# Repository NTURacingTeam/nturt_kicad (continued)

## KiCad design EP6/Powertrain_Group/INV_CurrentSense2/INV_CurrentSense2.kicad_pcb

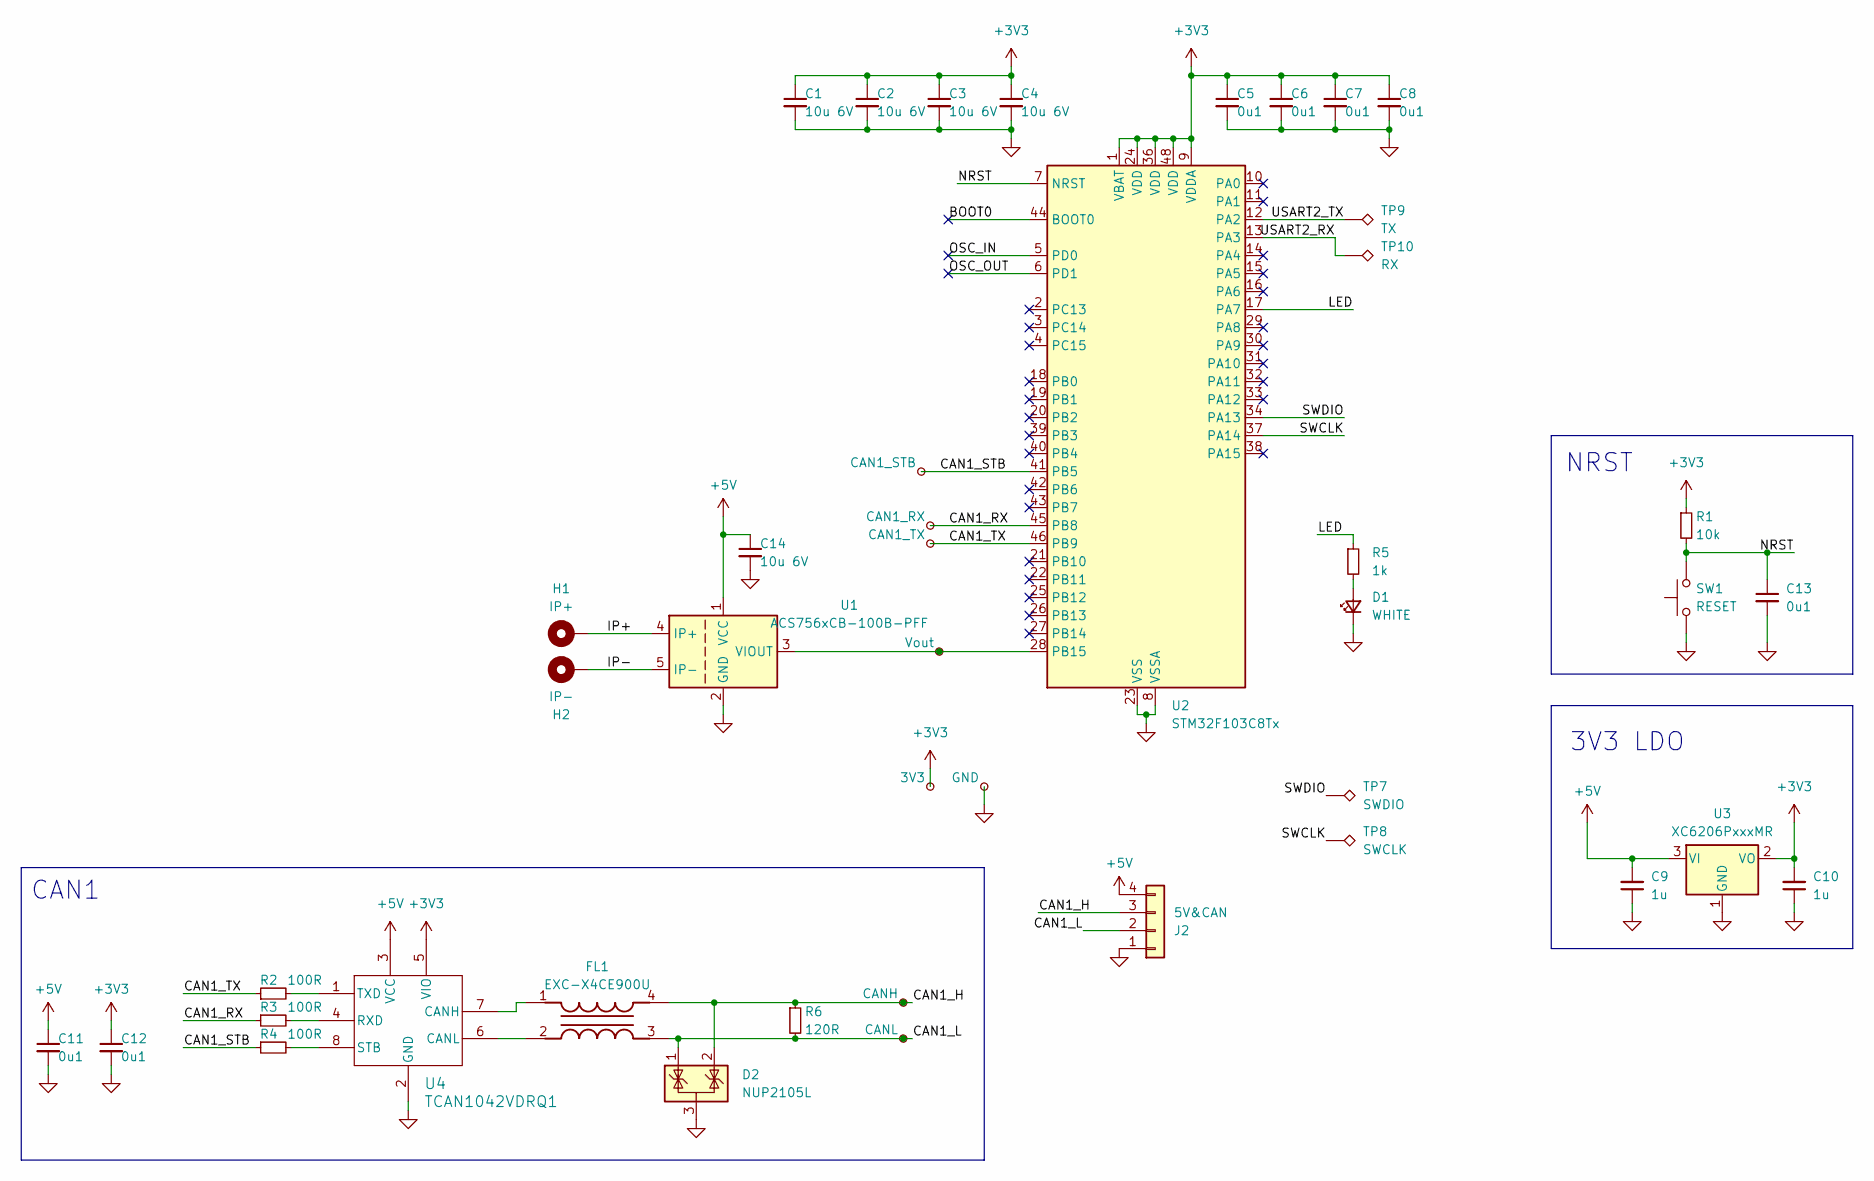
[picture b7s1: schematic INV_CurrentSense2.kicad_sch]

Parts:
C1, C2, C3, C4, C14: 10u 6V; C_0402_1005Metric
C5, C6, C7, C8, C11, C12, C13: 0u1; C_0402_1005Metric
C9, C10: 1u; C_0402_1005Metric
D1: WHITE; LED_0603_1608Metric
D2: NUP2105L; SOT-23
FL1: EXC-X4CE900U; EXCX4CE900U; Mouser Part Number 667-EXC-X4CE900U
H1: IP+; MountingHole_5.5mm_Pad_Via_15mm_square
H2: IP-; MountingHole_5.5mm_Pad_Via
J2: 5V&CAN; JST_XH_S4B-XH-A_1x04_P2.50mm_Horizontal
R1: 10k; R_0402_1005Metric
R2, R3, R4: 100R; R_0402_1005Metric
R5: 1k; R_0603_1608Metric
R6: 120R; R_0402_1005Metric
SW1: RESET; SW_Tactile_SPST_NO_Straight_CK_PTS636Sx25SMTRLFS
TP1: Vout; TestPoint_THTPad_D1.0mm_Drill0.5mm
TP2: CAN1_STB; TestPoint_THTPad_D1.0mm_Drill0.5mm
TP3: CANH; TestPoint_Pad_1.0x1.0mm
TP4: CANL; TestPoint_Pad_1.0x1.0mm
TP5: CAN1_RX; TestPoint_THTPad_D1.0mm_Drill0.5mm
TP6: CAN1_TX; TestPoint_THTPad_D1.0mm_Drill0.5mm
TP7: SWDIO; TestPoint_Pad_1.5x1.5mm
TP8: SWCLK; TestPoint_Pad_1.5x1.5mm
TP9: TX; TestPoint_Pad_1.0x1.0mm
TP10: RX; TestPoint_Pad_1.0x1.0mm
TP11: 3V3; TestPoint_THTPad_D1.0mm_Drill0.5mm
TP12: GND; TestPoint_THTPad_D1.0mm_Drill0.5mm
U1: ACS756xCB-100B-PFF; Allegro_CB_PFF
U2: STM32F103C8Tx; LQFP-48_7x7mm_P0.5mm
U3: XC6206PxxxMR; SOT-23-3
U4: TCAN1042VDRQ1; SOIC-8_3.9x4.9mm_P1.27mm

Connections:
+3V3: C1.1, C2.1, C3.1, C4.1, C5.1, C6.1, C7.1, C8.1, C10.2, C12.1, R1.1, TP11.1, U2.1 (VBAT), U2.9 (VDDA), U2.24 (VDD), U2.36 (VDD), U2.48 (VDD), U3.2 (VO), U4.5 (VIO)
+5V: C9.2, C11.1, C14.1, J2.4, U1.1 (VCC), U3.3 (VI), U4.3 (VCC)
/BOOT0: U2.44 (BOOT0)
/CAN1_H: D2.2 (K), FL1.4, J2.3, R6.1, TP3.1
/CAN1_L: D2.1 (K), FL1.3, J2.2, R6.2, TP4.1
/CAN1_RX: R3.1, TP5.1, U2.45 (PB8)
/CAN1_STB: R4.1, TP2.1, U2.41 (PB5)
/CAN1_TX: R2.1, TP6.1, U2.46 (PB9)
/IP+: H1.1, U1.4 (IP+)
/IP-: H2.1, U1.5 (IP-)
/LED: R5.1, U2.17 (PA7)
/NRST: C13.1, R1.2, SW1.2, U2.7 (NRST)
/OSC_IN: U2.5 (PD0)
/OSC_OUT: U2.6 (PD1)
/SWCLK: TP8.1, U2.37 (PA14)
/SWDIO: TP7.1, U2.34 (PA13)
/USART2_RX: TP10.1, U2.13 (PA3)
/USART2_TX: TP9.1, U2.12 (PA2)
GND: C1.2, C2.2, C3.2, C4.2, C5.2, C6.2, C7.2, C8.2, C9.1, C10.1, C11.2, C12.2, C13.2, C14.2, D1.1 (K), D2.3 (A), J2.1, SW1.1, TP12.1, U1.2 (GND), U2.8 (VSSA), U2.23 (VSS), U2.35 (VSS), U2.47 (VSS), U3.1 (GND), U4.2 (GND)
unnamed: D1.2 (A), R5.2
unnamed: TP1.1, U1.3 (VIOUT), U2.28 (PB15)
unnamed: FL1.1, U4.7 (CANH)
unnamed: FL1.2, U4.6 (CANL)
unnamed: R3.2, U4.4 (RXD)
unnamed: R4.2, U4.8 (STB)
unnamed: R2.2, U4.1 (TXD)

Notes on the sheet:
3V3 LDO
CAN1
NRST

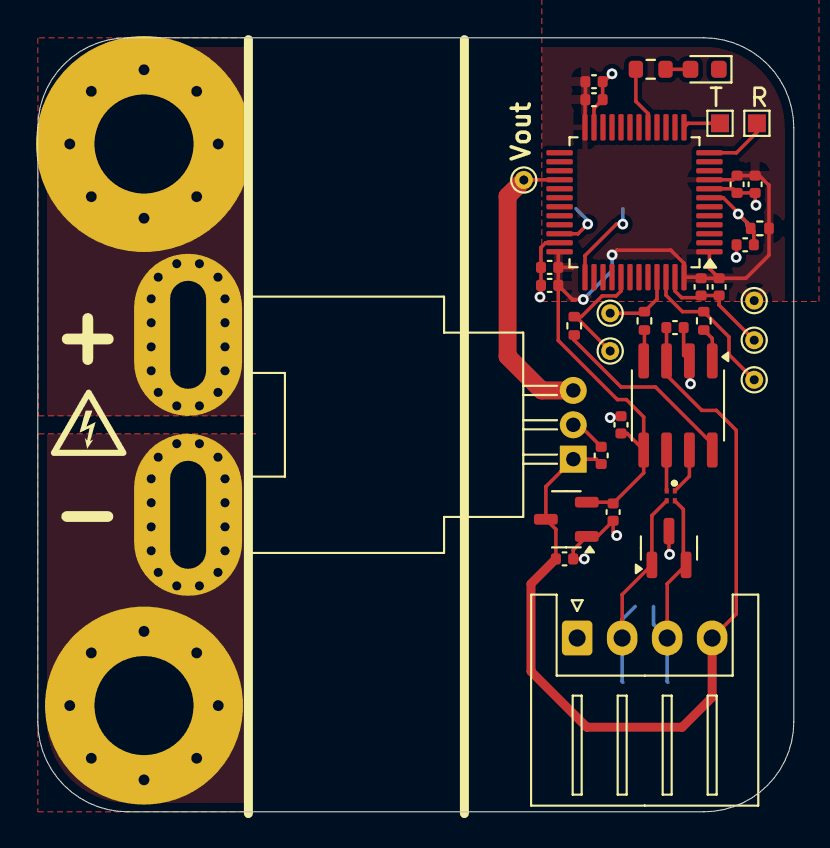
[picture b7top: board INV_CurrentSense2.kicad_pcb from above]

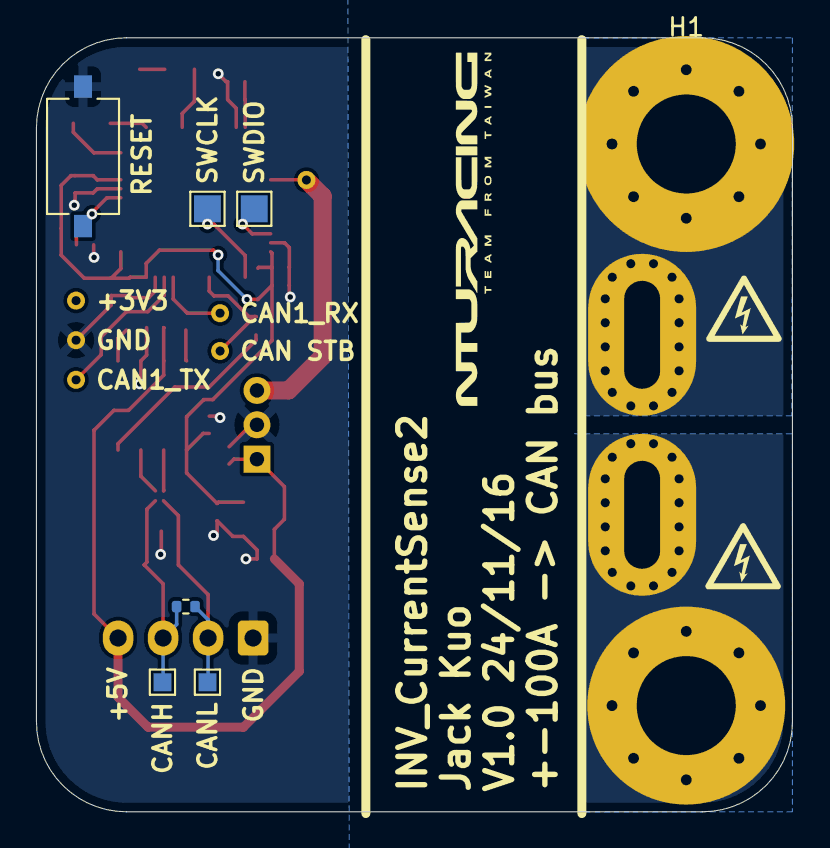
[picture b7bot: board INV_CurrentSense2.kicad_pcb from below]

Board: 2 copper layers, 42.0 x 43.0 mm, 43 parts (7 on the bottom side), 23 nets.

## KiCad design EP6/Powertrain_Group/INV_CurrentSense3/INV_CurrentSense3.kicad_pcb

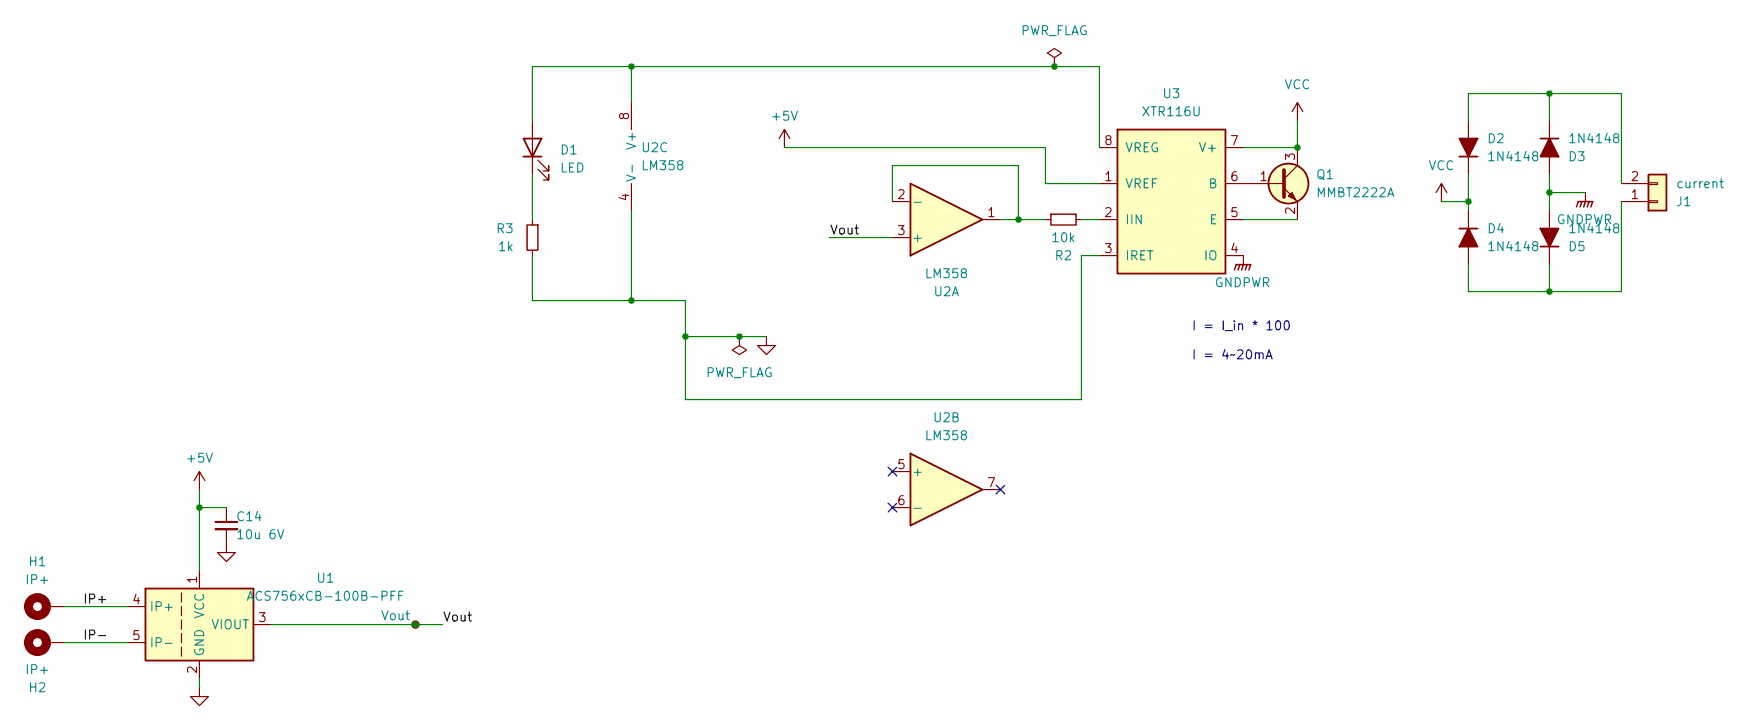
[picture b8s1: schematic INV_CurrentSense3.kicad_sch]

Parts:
C14: 10u 6V; C_0402_1005Metric
D1: LED; LED_0603_1608Metric
D2, D3, D4, D5: 1N4148; D_SOD-323
H1: IP+; MountingHole_5.5mm_Pad_Via_15mm_square
H2: IP+; MountingHole_5.5mm_Pad_Via
J1: current; JST_XH_S2B-XH-A_1x02_P2.50mm_Horizontal; Part Number 1-0201FBV0T
Q1: MMBT2222A; SOT-23
R2: 10k; R_0402_1005Metric
R3: 1k; R_0402_1005Metric
TP1: Vout; TestPoint_THTPad_D1.0mm_Drill0.5mm
U1: ACS756xCB-100B-PFF; Allegro_CB_PFF
U2: LM358; SOIC-8_3.9x4.9mm_P1.27mm
U3: XTR116U; SOIC-8_3.9x4.9mm_P1.27mm

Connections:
+5V: C14.1, U1.1 (VCC), U3.1 (VREF)
/IP+: H1.1, U1.4 (IP+)
/IP-: H2.1, U1.5 (IP-)
/Vout: TP1.1, U1.3 (VIOUT), U2.3 (+)
GND: C14.2, R3.2, U1.2 (GND), U2.4 (V-), U3.3 (IRET)
GNDPWR: D3.2 (A), D5.2 (A), U3.4 (IO)
unnamed: D1.2 (A), U2.8 (V+), U3.8 (VREG)
unnamed: D1.1 (K), R3.1
unnamed: D2.2 (A), D3.1 (K), J1.2
unnamed: D4.2 (A), D5.1 (K), J1.1
unnamed: Q1.1 (B), U3.6 (B)
unnamed: Q1.2 (E), U3.5 (E)
unnamed: R2.1, U2.1, U2.2 (-)
unnamed: R2.2, U3.2 (IIN)
VCC: D2.1 (K), D4.1 (K), Q1.3 (C), U3.7 (V+)

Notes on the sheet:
I = I_in * 100 I = 4~20mA

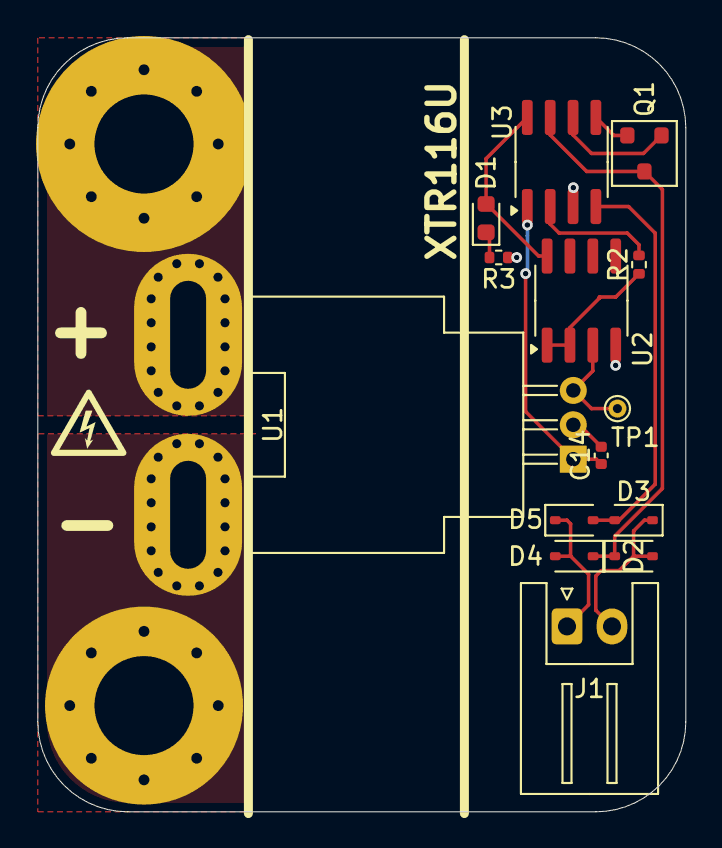
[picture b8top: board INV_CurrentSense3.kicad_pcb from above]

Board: 2 copper layers, 36.0 x 43.0 mm, 16 parts (1 on the bottom side), 15 nets.
